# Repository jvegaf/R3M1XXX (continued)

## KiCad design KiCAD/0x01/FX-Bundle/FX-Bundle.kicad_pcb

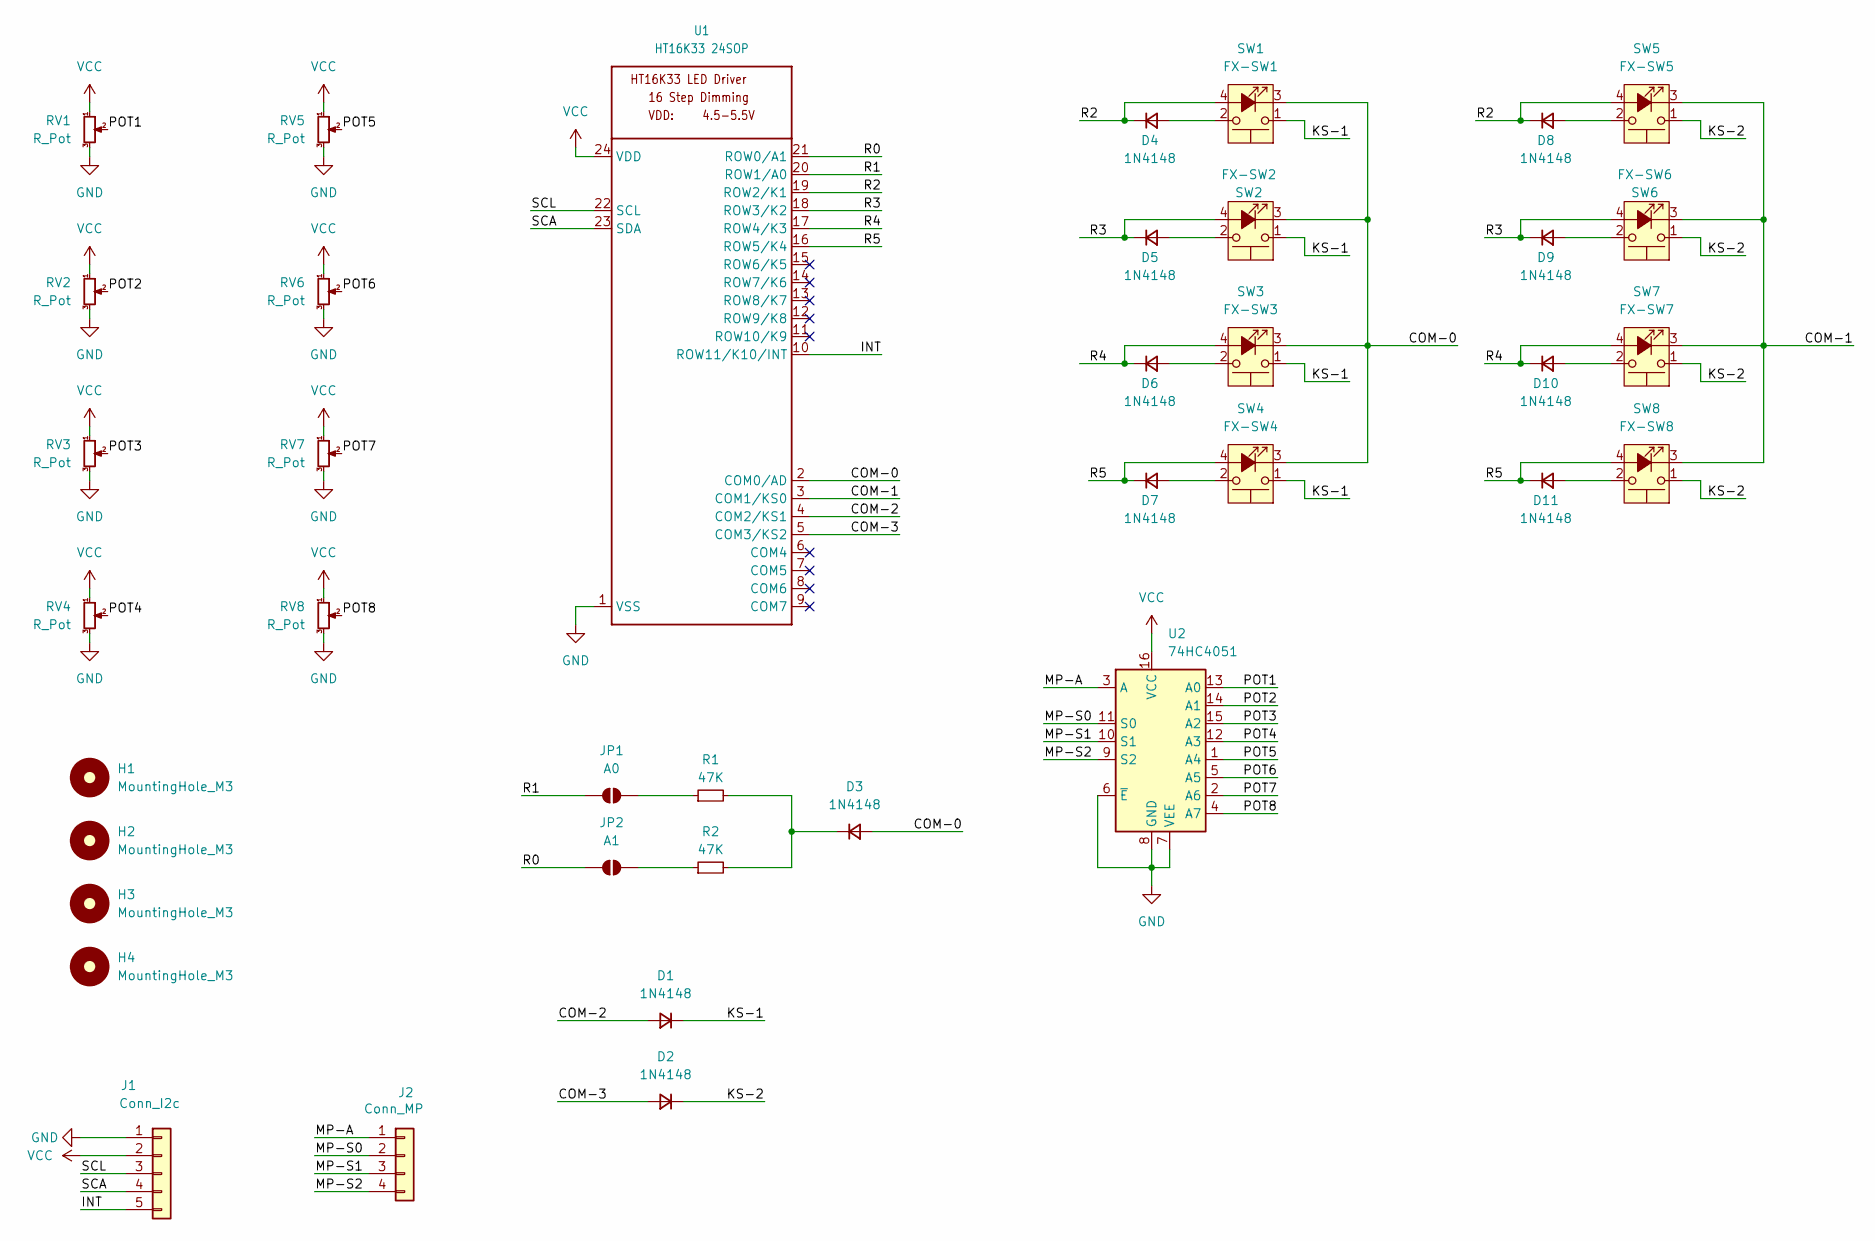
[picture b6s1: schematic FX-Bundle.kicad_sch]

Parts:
D1, D2, D3, D4, D5, D6, D7, D8, D9, D10, D11: 1N4148; D_SOD-123
H1, H2, H3, H4: MountingHole_M3; MountingHole_3.2mm_M3
J1: Conn_I2c; Hirose_DF13-05P-1.25DSA_1x05_P1.25mm_Vertical
J2: Conn_MP; Hirose_DF13-04P-1.25DSA_1x04_P1.25mm_Vertical
JP1: A0; SolderJumper-2_P1.3mm_Open_RoundedPad1.0x1.5mm
JP2: A1; SolderJumper-2_P1.3mm_Open_RoundedPad1.0x1.5mm
R1, R2: 47K; R_0805_2012Metric_Pad1.20x1.40mm_HandSolder
RV1, RV2, RV3, RV4, RV5, RV6, RV7, RV8: R_Pot; Potentiometer_Bourns_PTV09A-1_Single_Vertical
SW1: FX-SW1; led switch
SW2: FX-SW2; led switch
SW3: FX-SW3; led switch
SW4: FX-SW4; led switch
SW5: FX-SW5; led switch
SW6: FX-SW6; led switch
SW7: FX-SW7; led switch
SW8: FX-SW8; led switch
U1: HT16K33 24SOP; SSOP-24_5.3x8.2mm_P0.65mm
U2: 74HC4051; TSSOP-16-1EP_4.4x5mm_P0.65mm_EP3x3mm

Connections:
/COM-0: D3.2 (A), SW1.3 (K), SW2.3 (K), SW3.3 (K), SW4.3 (K), U1.2 (COM0/AD)
/COM-1: SW5.3 (K), SW6.3 (K), SW7.3 (K), SW8.3 (K), U1.3 (COM1/KS0)
/COM-2: D1.2 (A), U1.4 (COM2/KS1)
/COM-3: D2.2 (A), U1.5 (COM3/KS2)
/INT: J1.5, U1.10 (ROW11/K10/INT)
/KS-1: D1.1 (K), SW1.1, SW2.1, SW3.1, SW4.1
/KS-2: D2.1 (K), SW5.1, SW6.1, SW7.1, SW8.1
/MP-A: J2.1, U2.3 (A)
/MP-S0: J2.2, U2.11 (S0)
/MP-S1: J2.3, U2.10 (S1)
/MP-S2: J2.4, U2.9 (S2)
/POT1: RV1.2, U2.13 (A0)
/POT2: RV2.2, U2.14 (A1)
/POT3: RV3.2, U2.15 (A2)
/POT4: RV4.2, U2.12 (A3)
/POT5: RV5.2, U2.1 (A4)
/POT6: RV6.2, U2.5 (A5)
/POT7: RV7.2, U2.2 (A6)
/POT8: RV8.2, U2.4 (A7)
/R0: JP2.1 (A), U1.21 (ROW0/A1)
/R1: JP1.1 (A), U1.20 (ROW1/A0)
/R2: D4.1 (K), D8.1 (K), SW1.4 (A), SW5.4 (A), U1.19 (ROW2/K1)
/R3: D5.1 (K), D9.1 (K), SW2.4 (A), SW6.4 (A), U1.18 (ROW3/K2)
/R4: D6.1 (K), D10.1 (K), SW3.4 (A), SW7.4 (A), U1.17 (ROW4/K3)
/R5: D7.1 (K), D11.1 (K), SW4.4 (A), SW8.4 (A), U1.16 (ROW5/K4)
/SCA: J1.4, U1.23 (SDA)
/SCL: J1.3, U1.22 (SCL)
GND: J1.1, RV1.3, RV2.3, RV3.3, RV4.3, RV5.3, RV6.3, RV7.3, RV8.3, U1.1 (VSS), U2.6 (~E), U2.7 (VEE), U2.8 (GND)
unnamed: D3.1 (K), R1.2, R2.2
unnamed: D4.2 (A), SW1.2
unnamed: D5.2 (A), SW2.2
unnamed: D6.2 (A), SW3.2
unnamed: D7.2 (A), SW4.2
unnamed: D8.2 (A), SW5.2
unnamed: D9.2 (A), SW6.2
unnamed: D10.2 (A), SW7.2
unnamed: D11.2 (A), SW8.2
unnamed: JP1.2 (B), R1.1
unnamed: JP2.2 (B), R2.1
VCC: J1.2, RV1.1, RV2.1, RV3.1, RV4.1, RV5.1, RV6.1, RV7.1, RV8.1, U1.24 (VDD), U2.16 (VCC)

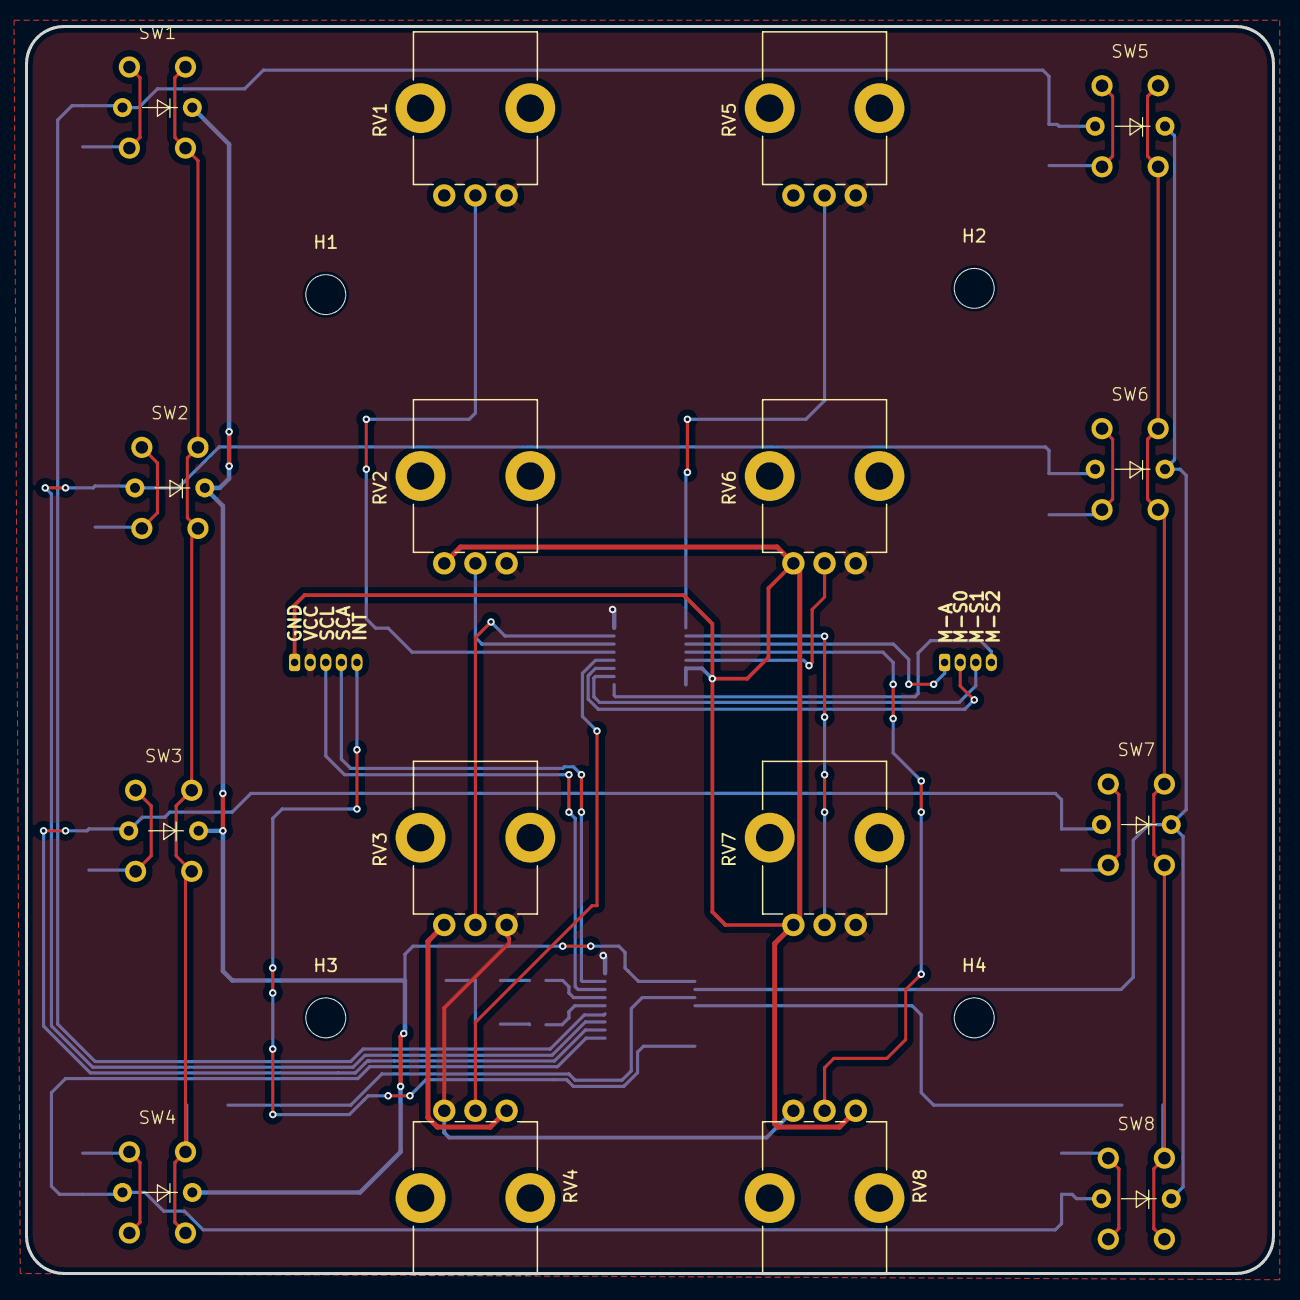
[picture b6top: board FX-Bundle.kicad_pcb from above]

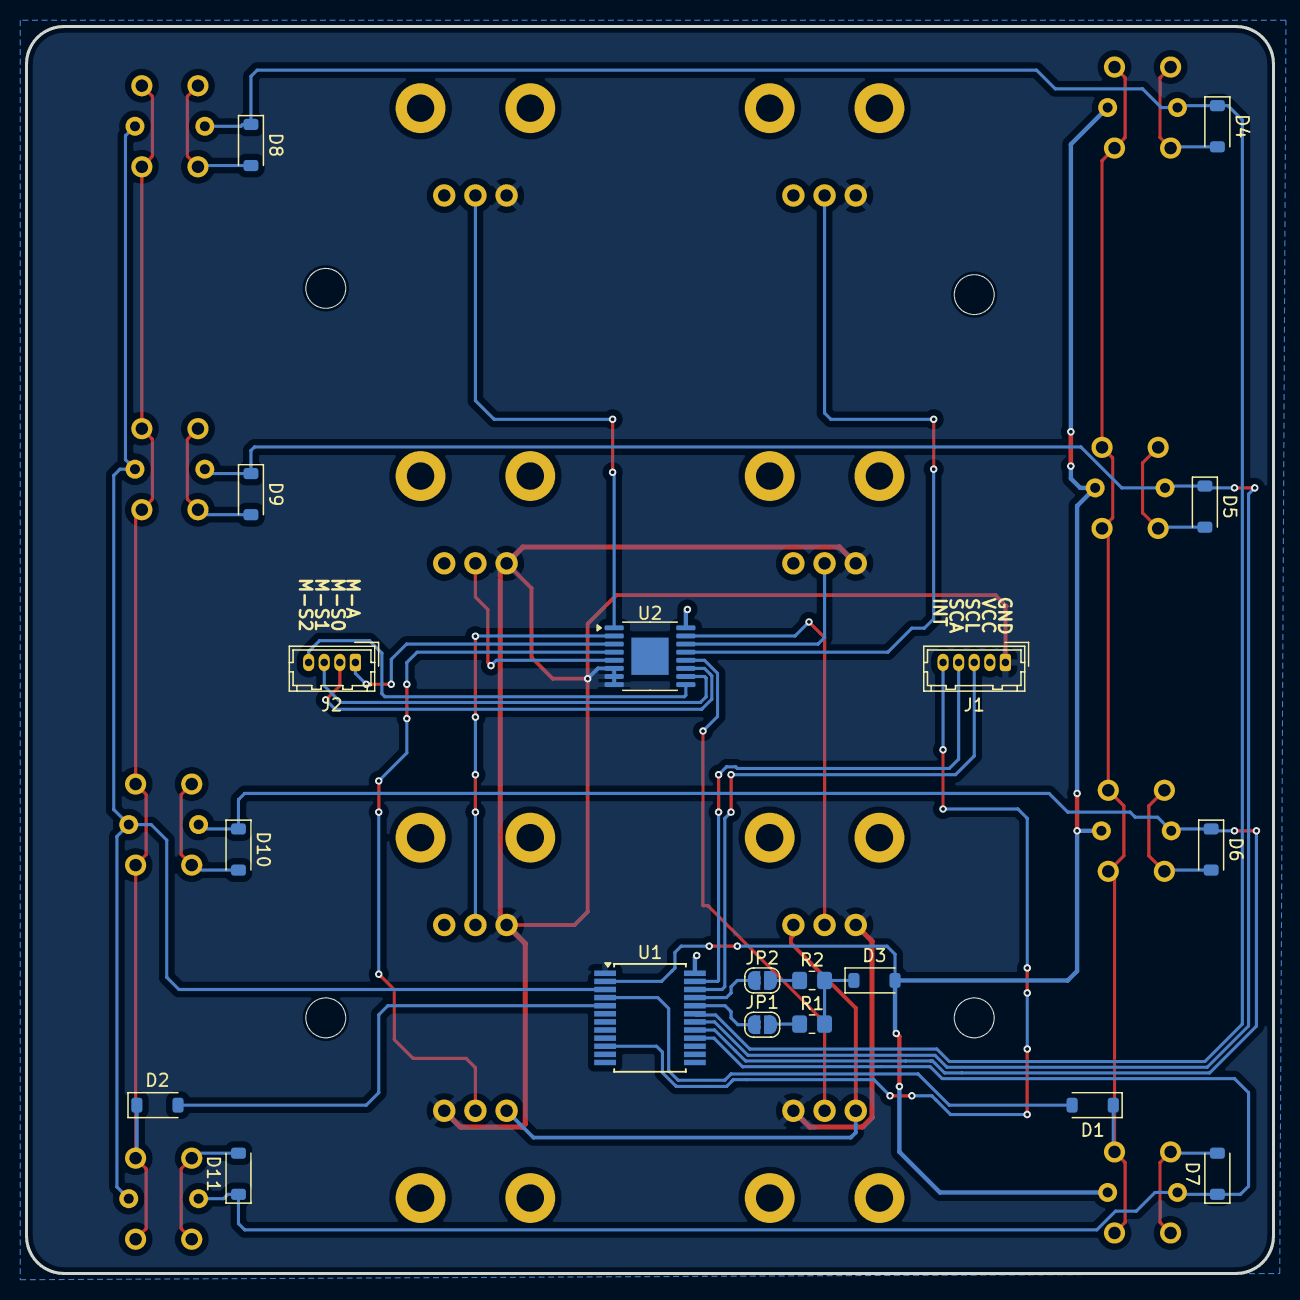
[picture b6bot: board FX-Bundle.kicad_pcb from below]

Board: 2 copper layers, 100.0 x 100.0 mm, 39 parts (19 on the bottom side), 40 nets.

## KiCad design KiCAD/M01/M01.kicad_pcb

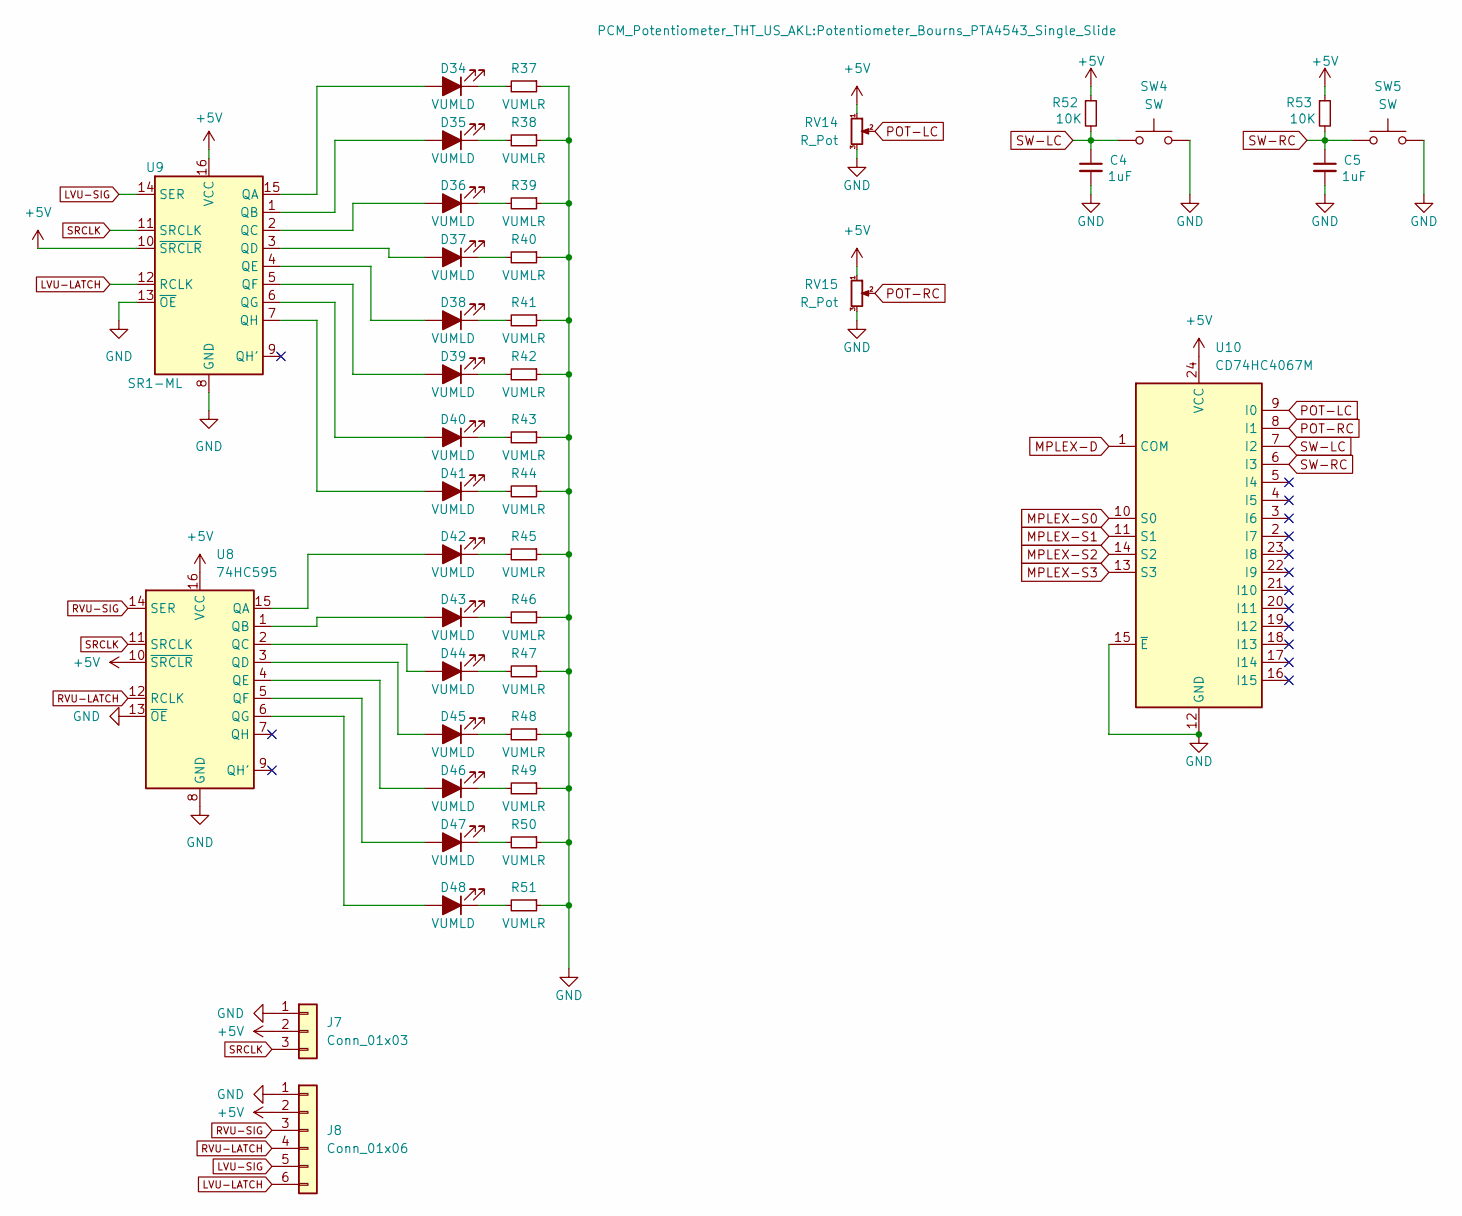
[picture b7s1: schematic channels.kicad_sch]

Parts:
C4, C5: 1uF; C_1206_3216Metric_Pad1.33x1.80mm_HandSolder
D34, D35, D36, D37, D38, D39, D40, D41, D42, D43, D44, D45, D46, D47, D48: VUMLD; LED_D3.0mm
J7: Conn_01x03; PinHeader_1x03_P2.54mm_Horizontal
J8: Conn_01x06; PinHeader_1x06_P2.54mm_Vertical
R37, R38, R39, R40, R41, R42, R43, R44, R45, R46, R47, R48, R49, R50, R51: VUMLR; R_1206_3216Metric_Pad1.30x1.75mm_HandSolder
R52, R53: 10K; R_1206_3216Metric_Pad1.30x1.75mm_HandSolder
RV14, RV15: R_Pot; Potentiometer_Bourns_PTA4543_Single_Slide
SW4, SW5: SW; SW_PUSH_6mm_H9.5mm
U8: 74HC595; SOIC-16W_5.3x10.2mm_P1.27mm
U9: SR1-ML; SOIC-16_3.9x9.9mm_P1.27mm
U10: CD74HC4067M; SOIC-24W_7.5x15.4mm_P1.27mm

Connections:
+5V: J7.2, J8.2, R52.1, R53.1, RV14.1, RV15.1, U8.10 (~SRCLR), U8.16 (VCC), U9.10 (~SRCLR), U9.16 (VCC), U10.24 (VCC); also elsewhere on the board
GND: C4.2, C5.2, J7.1, J8.1, R37.1, R38.1, R39.1, R40.1, R41.1, R42.1, R43.1, R44.1, R45.1, R46.1, R47.1, R48.1, R49.1, R50.1, R51.1, RV14.3, RV15.3, SW4.2, SW5.2, U8.8 (GND), U8.13 (~OE), U9.8 (GND), U9.13 (~OE), U10.12 (GND), U10.15 (~E); also elsewhere on the board
LVU-LATCH: J8.6, U9.12 (RCLK)
LVU-SIG: J8.5, U9.14 (SER)
MPLEX-D: U10.1 (COM)
MPLEX-S0: U10.10 (S0); also elsewhere on the board
MPLEX-S1: U10.11 (S1); also elsewhere on the board
MPLEX-S2: U10.14 (S2); also elsewhere on the board
MPLEX-S3: U10.13 (S3); also elsewhere on the board
unnamed: D34.2 (A), U9.15 (QA)
unnamed: D34.1 (K), R37.2
unnamed: D35.2 (A), U9.1 (QB)
unnamed: D35.1 (K), R38.2
unnamed: D36.2 (A), U9.2 (QC)
unnamed: D36.1 (K), R39.2
unnamed: D37.2 (A), U9.3 (QD)
unnamed: D37.1 (K), R40.2
unnamed: D38.2 (A), U9.4 (QE)
unnamed: D38.1 (K), R41.2
unnamed: D39.2 (A), U9.5 (QF)
unnamed: D39.1 (K), R42.2
unnamed: D40.2 (A), U9.6 (QG)
unnamed: D40.1 (K), R43.2
unnamed: D41.2 (A), U9.7 (QH)
unnamed: D41.1 (K), R44.2
unnamed: D42.2 (A), U8.15 (QA)
unnamed: D42.1 (K), R45.2
unnamed: D43.2 (A), U8.1 (QB)
unnamed: D43.1 (K), R46.2
unnamed: D44.2 (A), U8.2 (QC)
unnamed: D44.1 (K), R47.2
unnamed: D45.2 (A), U8.3 (QD)
unnamed: D45.1 (K), R48.2
unnamed: D46.2 (A), U8.4 (QE)
unnamed: D46.1 (K), R49.2
unnamed: D47.2 (A), U8.5 (QF)
unnamed: D47.1 (K), R50.2
unnamed: D48.2 (A), U8.6 (QG)
unnamed: D48.1 (K), R51.2
POT-LC: RV14.2, U10.9 (I0)
POT-RC: RV15.2, U10.8 (I1)
RVU-LATCH: J8.4, U8.12 (RCLK)
RVU-SIG: J8.3, U8.14 (SER)
SRCLK: J7.3, U8.11 (SRCLK), U9.11 (SRCLK); also elsewhere on the board
SW-LC: C4.1, R52.2, SW4.1, U10.7 (I2)
SW-RC: C5.1, R53.2, SW5.1, U10.6 (I3)

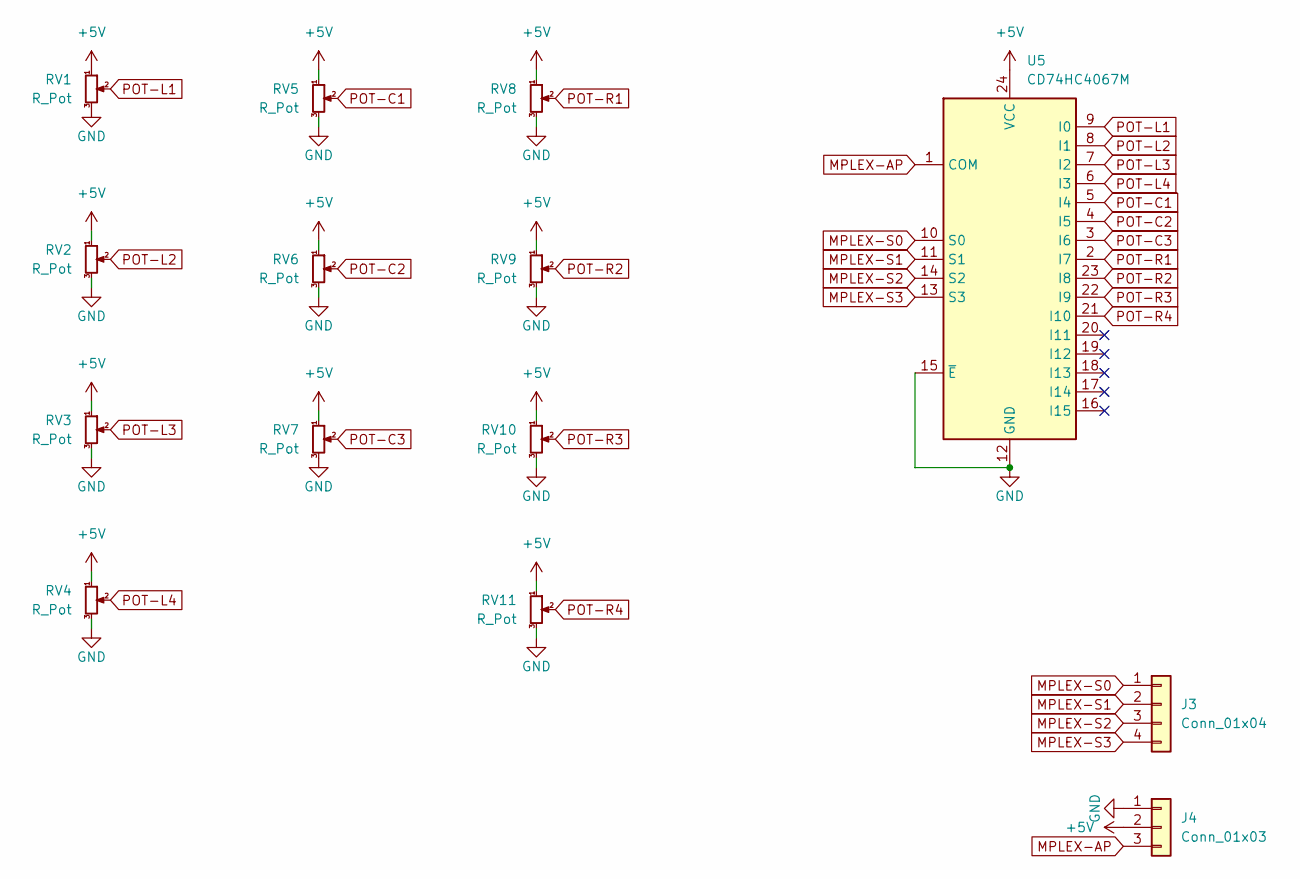
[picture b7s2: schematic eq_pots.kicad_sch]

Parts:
J3: Conn_01x04; PinHeader_1x04_P2.54mm_Vertical
J4: Conn_01x03; PinHeader_1x03_P2.54mm_Vertical
RV1, RV2, RV3, RV4, RV5, RV6, RV7, RV8, RV9, RV10, RV11: R_Pot; Potentiometer_Bourns_PTV09A-1_Single_Vertical
U5: CD74HC4067M; SOIC-24W_7.5x15.4mm_P1.27mm

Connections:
+5V: J4.2, RV1.1, RV2.1, RV3.1, RV4.1, RV5.1, RV6.1, RV7.1, RV8.1, RV9.1, RV10.1, RV11.1, U5.24 (VCC); also elsewhere on the board
/EQ Pots/MPLEX-AP: J4.3, U5.1 (COM)
/EQ Pots/MPLEX-S0: J3.1, U5.10 (S0)
/EQ Pots/MPLEX-S1: J3.2, U5.11 (S1)
/EQ Pots/MPLEX-S2: J3.3, U5.14 (S2)
/EQ Pots/MPLEX-S3: J3.4, U5.13 (S3)
/EQ Pots/POT-C2: RV6.2, U5.4 (I5)
/EQ Pots/POT-C3: RV7.2, U5.3 (I6)
/EQ Pots/POT-L1: RV1.2, U5.9 (I0), U5.17 (I14)
/EQ Pots/POT-L2: RV2.2, U5.8 (I1), U5.16 (I15)
/EQ Pots/POT-L3: RV3.2, U5.7 (I2)
/EQ Pots/POT-L4: RV4.2, U5.6 (I3)
/EQ Pots/POT-R1: RV8.2, U5.2 (I7), U5.19 (I12)
/EQ Pots/POT-R3: RV10.2, U5.22 (I9)
GND: J4.1, RV1.3, RV2.3, RV3.3, RV4.3, RV5.3, RV6.3, RV7.3, RV8.3, RV9.3, RV10.3, RV11.3, U5.12 (GND), U5.15 (~E); also elsewhere on the board

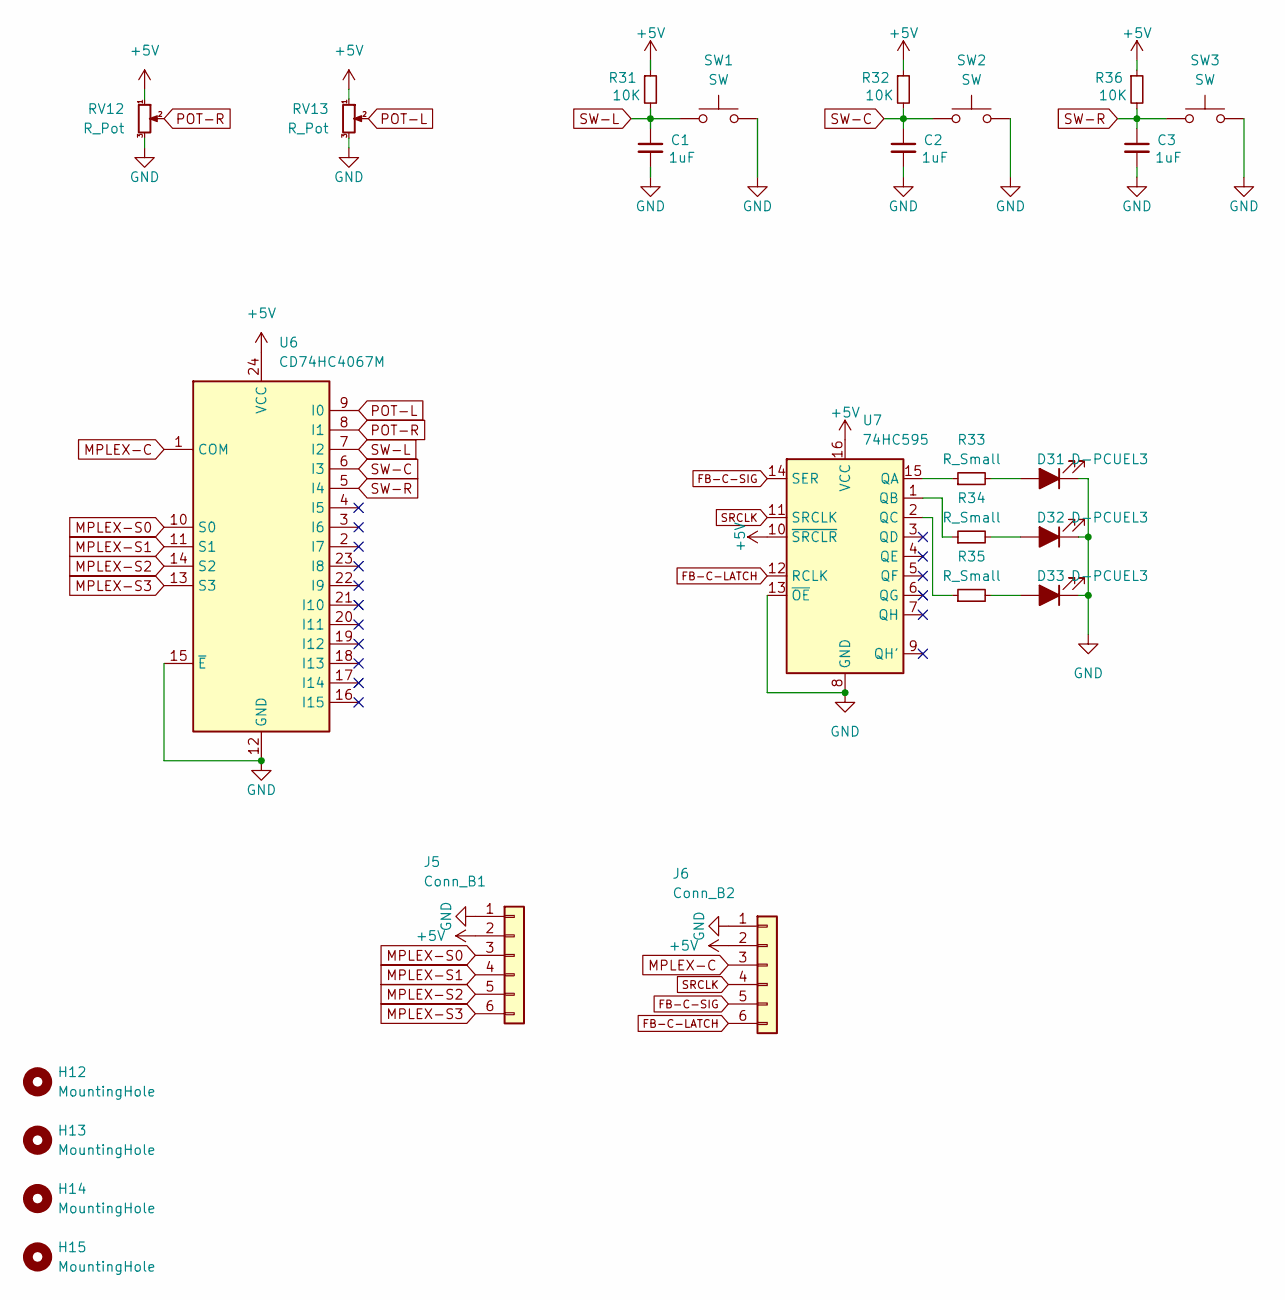
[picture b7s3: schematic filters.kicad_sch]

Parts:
C1, C2, C3: 1uF; C_1206_3216Metric_Pad1.33x1.80mm_HandSolder
D31, D32, D33: D-PCUEL3; LED_1206_3216Metric_Pad1.42x1.75mm_HandSolder
H12, H13, H14, H15: MountingHole; MountingHole_3.2mm_M3
J5: Conn_B1; PinHeader_1x06_P2.54mm_Vertical
J6: Conn_B2; PinHeader_1x06_P2.54mm_Vertical
R31, R32, R36: 10K; R_1206_3216Metric_Pad1.30x1.75mm_HandSolder
R33, R34, R35: R_Small; R_1206_3216Metric_Pad1.30x1.75mm_HandSolder
RV12, RV13: R_Pot; Potentiometer_Bourns_PTV09A-1_Single_Vertical
SW1, SW2, SW3: SW; SW_PUSH_6mm_H9.5mm
U6: CD74HC4067M; SOIC-24W_7.5x15.4mm_P1.27mm
U7: 74HC595; SOIC-16W_5.3x10.2mm_P1.27mm

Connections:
+5V: J5.2, J6.2, R31.1, R32.1, R36.1, RV12.1, RV13.1, U6.24 (VCC), U7.10 (~SRCLR), U7.16 (VCC); also elsewhere on the board
FB-C-LATCH: J6.6, U7.12 (RCLK)
FB-C-SIG: J6.5, U7.14 (SER)
GND: C1.2, C2.2, C3.2, D31.1 (K), D32.1 (K), D33.1 (K), J5.1, J6.1, RV12.3, RV13.3, SW1.2, SW2.2, SW3.2, U6.12 (GND), U6.15 (~E), U7.8 (GND), U7.13 (~OE); also elsewhere on the board
MPLEX-C: J6.3, U6.1 (COM)
MPLEX-S0: J5.3, U6.10 (S0); also elsewhere on the board
MPLEX-S1: J5.4, U6.11 (S1); also elsewhere on the board
MPLEX-S2: J5.5, U6.14 (S2); also elsewhere on the board
MPLEX-S3: J5.6, U6.13 (S3); also elsewhere on the board
unnamed: D31.2 (A), R33.2
unnamed: D32.2 (A), R34.2
unnamed: D33.2 (A), R35.2
unnamed: R33.1, U7.15 (QA)
unnamed: R34.1, U7.1 (QB)
unnamed: R35.1, U7.2 (QC)
POT-L: RV13.2, U6.9 (I0)
POT-R: RV12.2, U6.8 (I1)
SRCLK: J6.4, U7.11 (SRCLK); also elsewhere on the board
SW-C: C2.1, R32.2, SW2.1, U6.6 (I3)
SW-L: C1.1, R31.2, SW1.1, U6.7 (I2)
SW-R: C3.1, R36.2, SW3.1, U6.5 (I4)

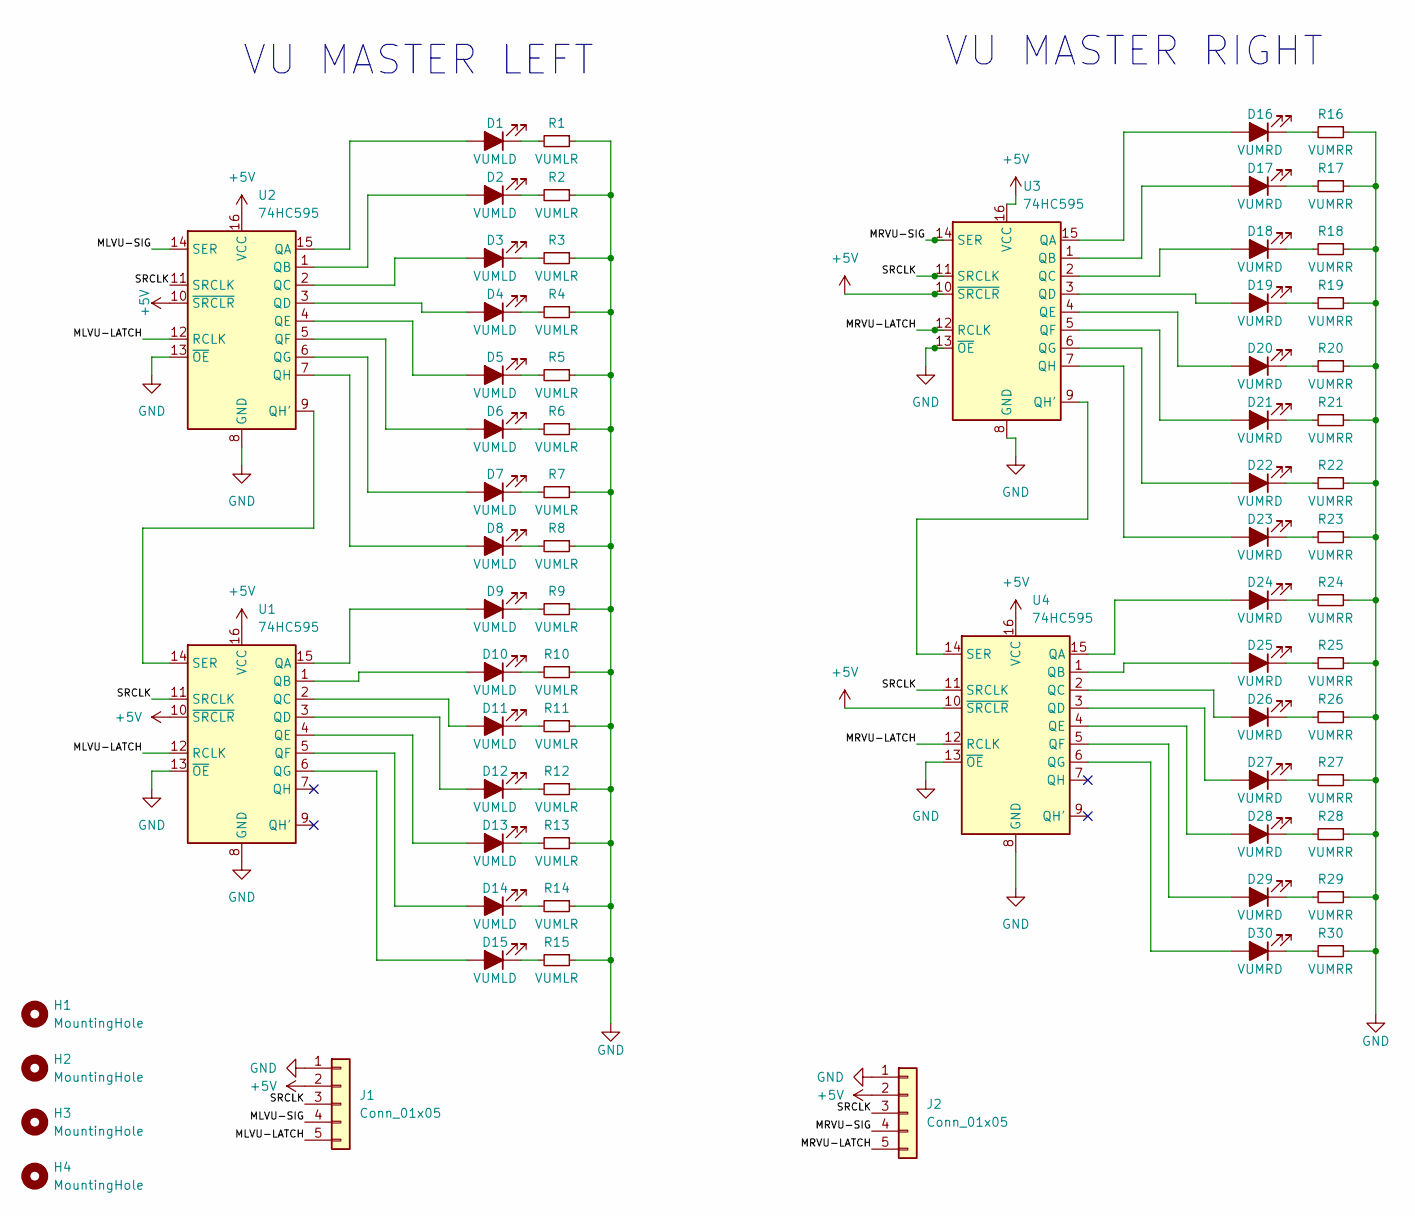
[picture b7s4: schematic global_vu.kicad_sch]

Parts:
D1, D2, D3, D4, D5, D6, D7, D8, D9, D10, D11, D12, D13, D14, D15: VUMLD; LED_D3.0mm
D16, D17, D18, D19, D20, D21, D22, D23, D24, D25, D26, D27, D28, D29, D30: VUMRD; LED_D3.0mm
H1, H2, H3, H4: MountingHole; MountingHole_3.2mm_M3
J1, J2: Conn_01x05; PinSocket_1x05_P2.54mm_Vertical
R1, R2, R3, R4, R5, R6, R7, R8, R9, R10, R11, R12, R13, R14, R15: VUMLR; R_1206_3216Metric_Pad1.30x1.75mm_HandSolder
R16, R17, R18, R19, R20, R21, R22, R23, R24, R25, R26, R27, R28, R29, R30: VUMRR; R_1206_3216Metric_Pad1.30x1.75mm_HandSolder
U1, U2, U3, U4: 74HC595; SOIC-16W_5.3x10.2mm_P1.27mm

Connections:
+5V: J1.2, J2.2, U1.10 (~SRCLR), U1.16 (VCC), U2.10 (~SRCLR), U2.16 (VCC), U3.10 (~SRCLR), U3.16 (VCC), U4.10 (~SRCLR), U4.16 (VCC); also elsewhere on the board
/Global VU/MLVU-LATCH: J1.5, U1.12 (RCLK), U2.12 (RCLK)
/Global VU/MLVU-SIG: J1.4, U2.14 (SER)
/Global VU/MRVU-LATCH: J2.5, U3.12 (RCLK), U4.12 (RCLK)
/Global VU/MRVU-SIG: J2.4, U3.14 (SER)
/Global VU/SRCLK: J1.3, J2.3, U1.11 (SRCLK), U2.11 (SRCLK), U3.11 (SRCLK), U4.11 (SRCLK)
GND: J1.1, J2.1, R1.1, R2.1, R3.1, R4.1, R5.1, R6.1, R7.1, R8.1, R9.1, R10.1, R11.1, R12.1, R13.1, R14.1, R15.1, R16.1, R17.1, R18.1, R19.1, R20.1, R21.1, R22.1, R23.1, R24.1, R25.1, R26.1, R27.1, R28.1, R29.1, R30.1, U1.8 (GND), U1.13 (~OE), U2.8 (GND), U2.13 (~OE), U3.8 (GND), U3.13 (~OE), U4.8 (GND), U4.13 (~OE); also elsewhere on the board
unnamed: D1.2 (A), U2.15 (QA)
unnamed: D1.1 (K), R1.2
unnamed: D2.2 (A), U2.1 (QB)
unnamed: D2.1 (K), R2.2
unnamed: D3.2 (A), U2.2 (QC)
unnamed: D3.1 (K), R3.2
unnamed: D4.2 (A), U2.3 (QD)
unnamed: D4.1 (K), R4.2
unnamed: D5.2 (A), U2.4 (QE)
unnamed: D5.1 (K), R5.2
unnamed: D6.2 (A), U2.5 (QF)
unnamed: D6.1 (K), R6.2
unnamed: D7.2 (A), U2.6 (QG)
unnamed: D7.1 (K), R7.2
unnamed: D8.2 (A), U2.7 (QH)
unnamed: D8.1 (K), R8.2
unnamed: D9.2 (A), U1.15 (QA)
unnamed: D9.1 (K), R9.2
unnamed: D10.2 (A), U1.1 (QB)
unnamed: D10.1 (K), R10.2
unnamed: D11.2 (A), U1.2 (QC)
unnamed: D11.1 (K), R11.2
unnamed: D12.2 (A), U1.3 (QD)
unnamed: D12.1 (K), R12.2
unnamed: D13.2 (A), U1.4 (QE)
unnamed: D13.1 (K), R13.2
unnamed: D14.2 (A), U1.5 (QF)
unnamed: D14.1 (K), R14.2
unnamed: D15.2 (A), U1.6 (QG)
unnamed: D15.1 (K), R15.2
unnamed: D16.2 (A), U3.15 (QA)
unnamed: D16.1 (K), R16.2
unnamed: D17.2 (A), U3.1 (QB)
unnamed: D17.1 (K), R17.2
unnamed: D18.2 (A), U3.2 (QC)
unnamed: D18.1 (K), R18.2
unnamed: D19.2 (A), U3.3 (QD)
unnamed: D19.1 (K), R19.2
unnamed: D20.2 (A), U3.4 (QE)
unnamed: D20.1 (K), R20.2
unnamed: D21.2 (A), U3.5 (QF)
unnamed: D21.1 (K), R21.2
unnamed: D22.2 (A), U3.6 (QG)
unnamed: D22.1 (K), R22.2
unnamed: D23.2 (A), U3.7 (QH)
unnamed: D23.1 (K), R23.2
unnamed: D24.2 (A), U4.15 (QA)
unnamed: D24.1 (K), R24.2
unnamed: D25.2 (A), U4.1 (QB)
unnamed: D25.1 (K), R25.2
unnamed: D26.2 (A), U4.2 (QC)
unnamed: D26.1 (K), R26.2
unnamed: D27.2 (A), U4.3 (QD)
unnamed: D27.1 (K), R27.2
unnamed: D28.2 (A), U4.4 (QE)
unnamed: D28.1 (K), R28.2
unnamed: D29.2 (A), U4.5 (QF)
unnamed: D29.1 (K), R29.2
unnamed: D30.2 (A), U4.6 (QG)
unnamed: D30.1 (K), R30.2
unnamed: U1.14 (SER), U2.9 (QH')
unnamed: U3.9 (QH'), U4.14 (SER)

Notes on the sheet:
VU MASTER LEFT
VU MASTER RIGHT

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
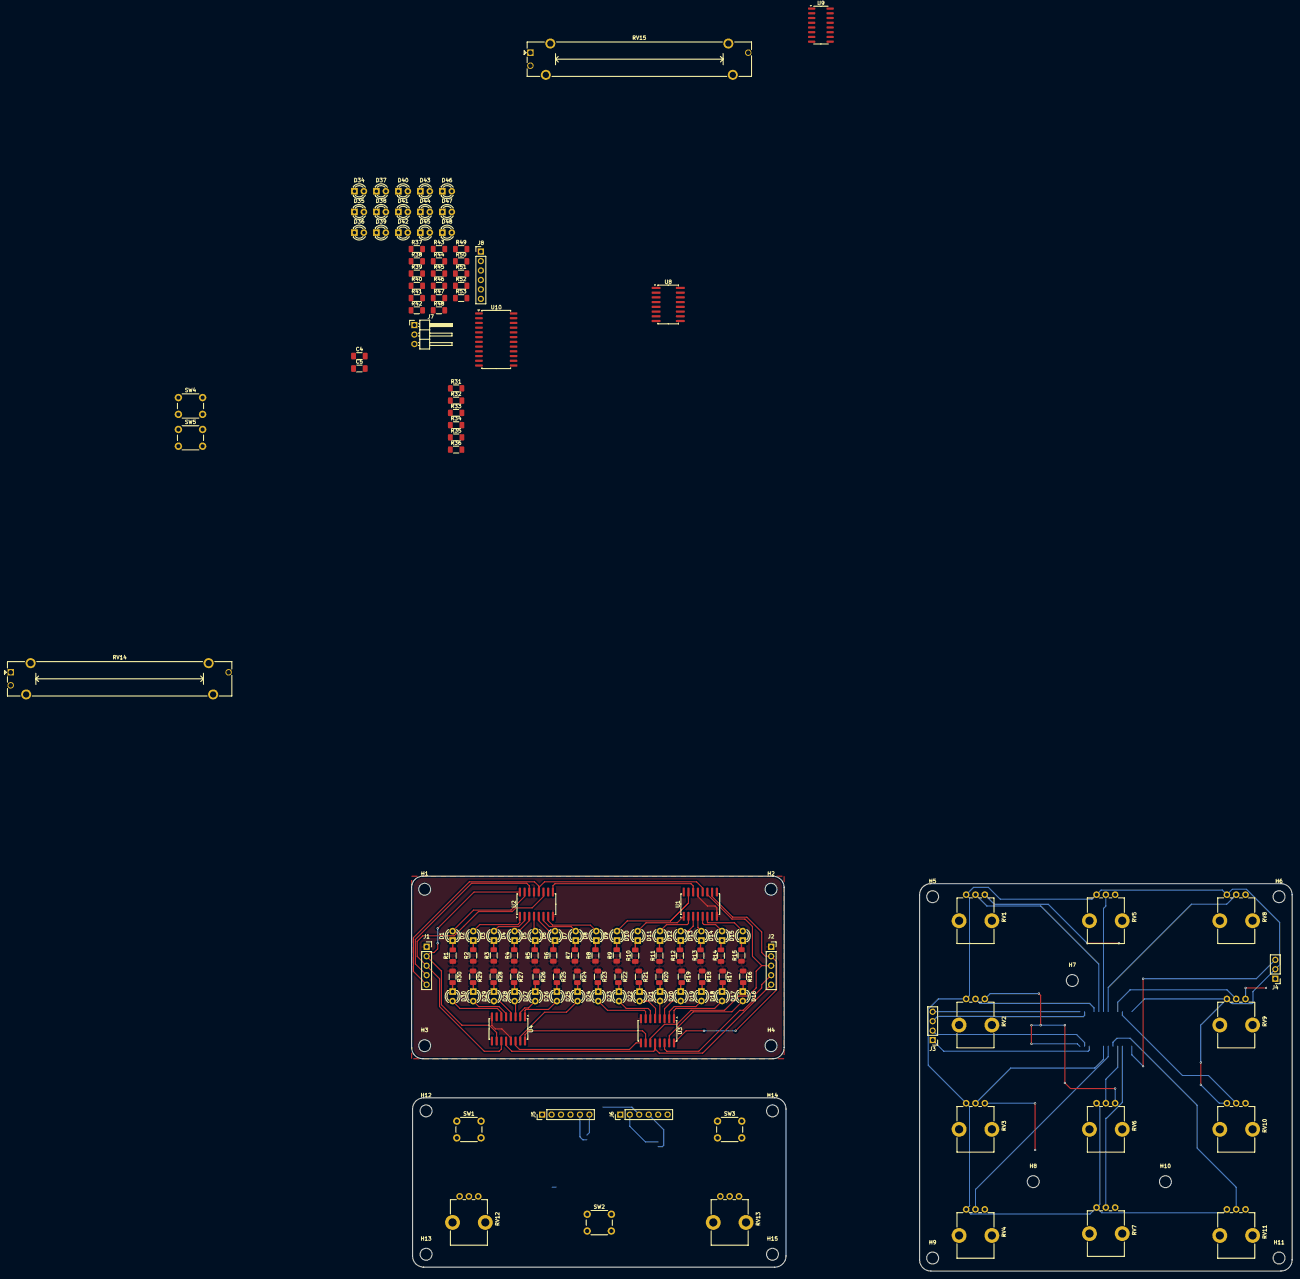
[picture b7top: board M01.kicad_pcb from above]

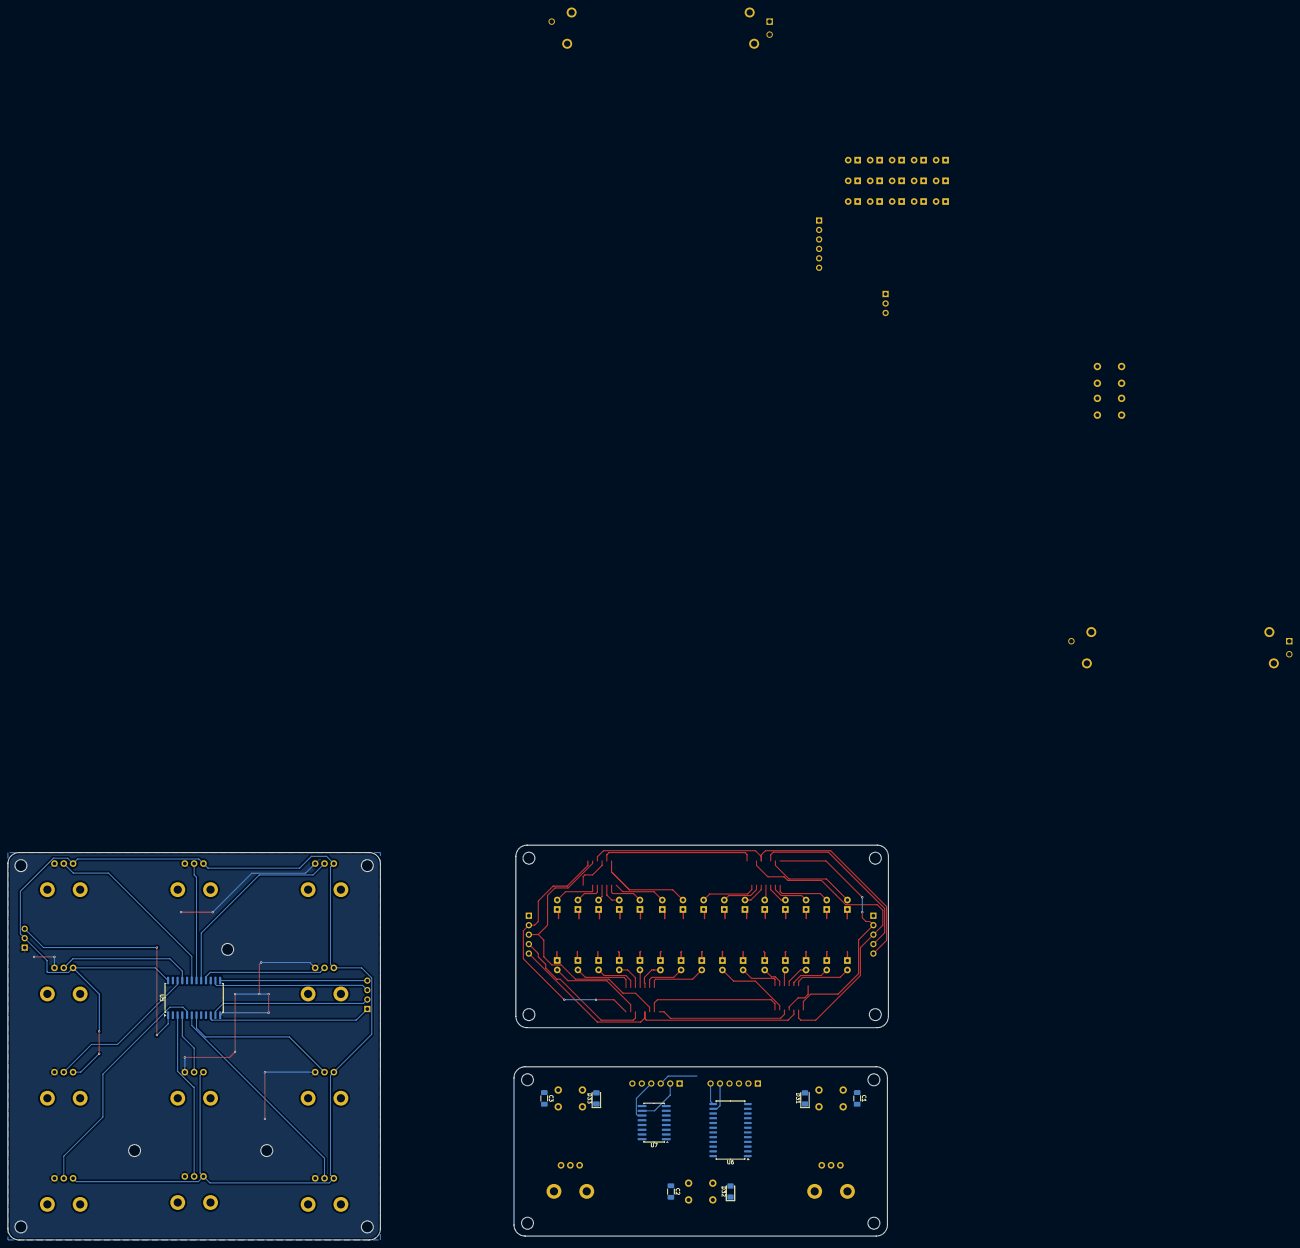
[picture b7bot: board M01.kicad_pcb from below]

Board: 2 copper layers, 236.4 x 106.0 mm, 159 parts (9 on the bottom side), 142 nets.

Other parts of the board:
H5, H6, H7, H8, H9, H10, H11: MountingHole; MountingHole_3.2mm_M3
